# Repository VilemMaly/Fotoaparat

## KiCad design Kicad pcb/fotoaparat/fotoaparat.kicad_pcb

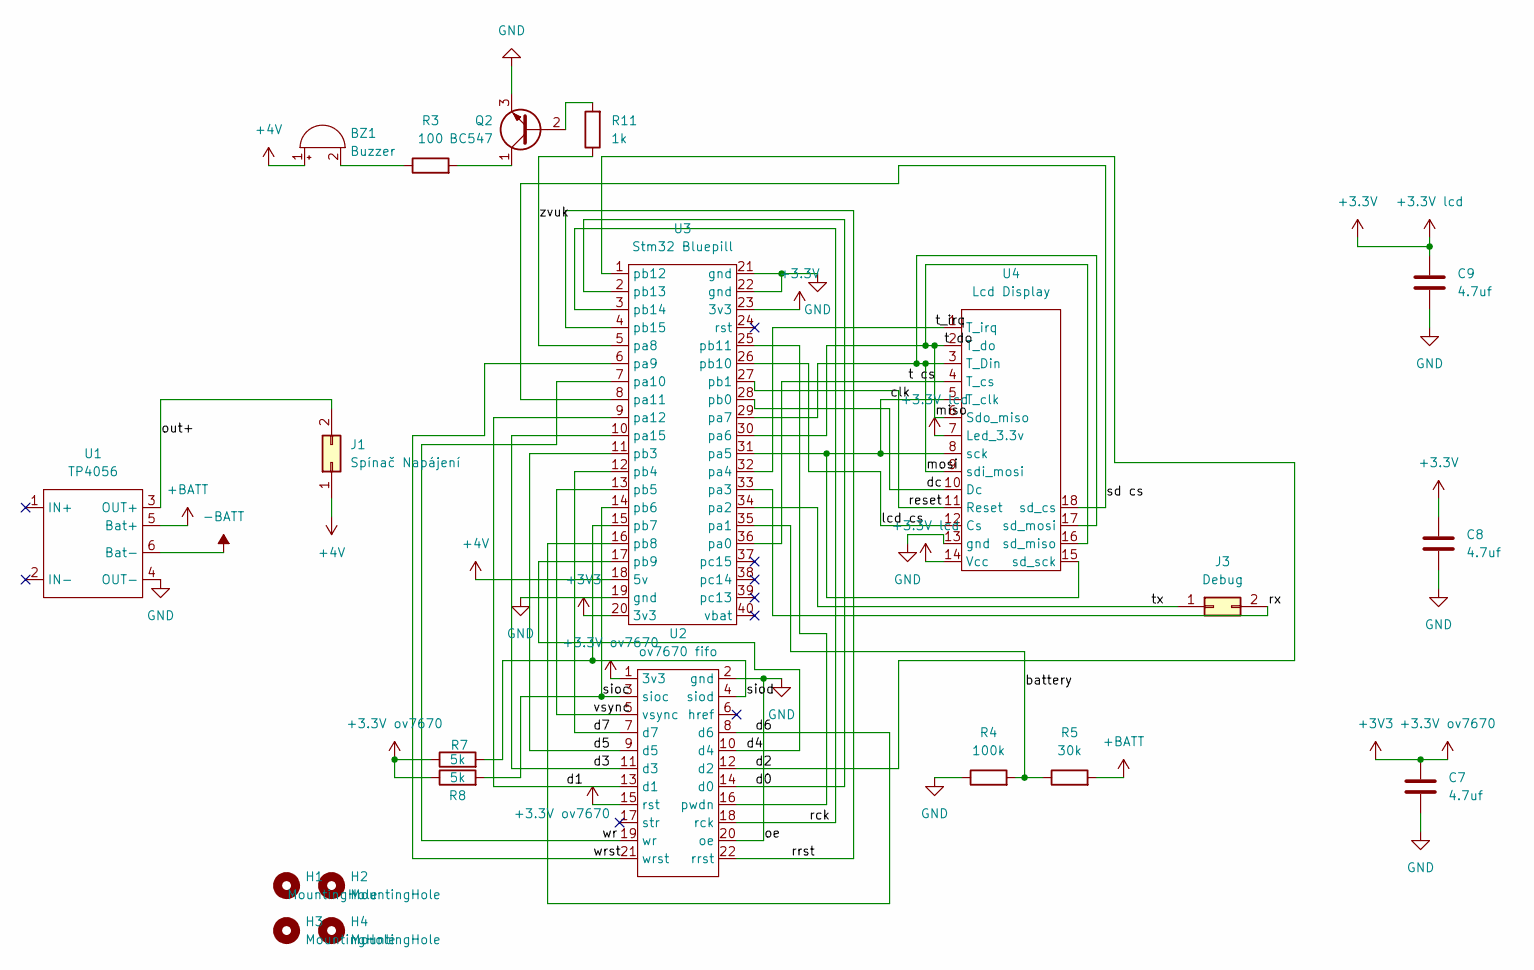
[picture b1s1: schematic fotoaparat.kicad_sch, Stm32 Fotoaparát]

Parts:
BZ1: Buzzer; Jiangsu
C7, C8, C9: 4.7uf; kondenzator
H1, H2, H3, H4: MountingHole; MountingHole_3.2mm_M3
J1: Spínač Napájení; txrx
J3: Debug; txrx
Q2: BC547; npnTHT
R3: 100; thtRESISTOR
R4: 100k; thtRESISTOR
R5: 30k; thtRESISTOR
R7, R8: 5k; thtRESISTOR
R11: 1k; thtRESISTOR
U1: TP4056
U2: ov7670 fifo; ov7670
U3: Stm32 Bluepill; Bluepill
U4: Lcd Display; ili9341

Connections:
+3.3V: C8.1, C9.1, U3.23 (3v3), U4.7 (Led_3.3v), U4.14 (Vcc)
+3.3V ov7670: C7.1, R7.1, R8.1, U2.1 (3v3), U2.15 (rst), U3.20 (3v3)
+4V: BZ1.1 (+), J1.1, U3.18 (5v)
+BATT: R5.2, U1.5 (Bat+)
-BATT: U1.6 (Bat-)
/battery: R4.2, R5.1, U3.35 (pa1)
/clk: U3.31 (pa5), U4.5 (T_clk), U4.8 (sck), U4.15 (sd_sck)
/d0: U2.14 (d0), U3.2 (pb13)
/d1: U2.13 (d1), U3.9 (pa12)
/d2: U2.12 (d2), U3.1 (pb12)
/d3: U2.11 (d3), U3.10 (pa15)
/d4: U2.10 (d4), U3.17 (pb9)
/d5: U2.9 (d5), U3.11 (pb3)
/d6: U2.8 (d6), U3.16 (pb8)
/d7: U2.7 (d7), U3.12 (pb4)
/dc: U3.28 (pb0), U4.10 (Dc)
/lcd cs: U3.26 (pb10), U4.12 (Cs)
/miso: U3.30 (pa6), U4.2 (T_do), U4.6 (Sdo_miso), U4.16 (sd_miso)
/mosi: U3.29 (pa7), U4.3 (T_Din), U4.9 (sdi_mosi), U4.17 (sd_mosi)
/out+: J1.2, U1.3 (OUT+)
/rck: U2.18 (rck), U3.3 (pb14)
/reset: U3.27 (pb1), U4.11 (Reset)
/rrst: U2.22 (rrst), U3.4 (pb15)
/rx: J3.2, U3.33 (pa3)
/sd cs: U3.8 (pa11), U4.18 (sd_cs)
/sioc: R8.2, U2.3 (sioc), U3.14 (pb6)
/siod: R7.2, U2.4 (siod), U3.15 (pb7)
/t cs: U3.36 (pa0), U4.4 (T_cs)
/t_irq: U3.32 (pa4), U4.1 (T_irq)
/tx: J3.1, U3.34 (pa2)
/vsync: U2.5 (vsync), U3.13 (pb5)
/wr: U2.19 (wr), U3.7 (pa10)
/wrst: U2.21 (wrst), U3.6 (pa9)
/zvuk: R11.1, U3.5 (pa8)
GND: C7.2, C8.2, C9.2, Q2.3 (E), R4.1, U1.4 (OUT-), U2.2 (gnd), U2.20 (oe), U3.19 (gnd), U3.21 (gnd), U3.22 (gnd), U4.13 (gnd)
unnamed: BZ1.2 (-), R3.1
unnamed: Q2.2 (B), R11.2
unnamed: Q2.1 (C), R3.2
unnamed: U2.16 (pwdn), U3.25 (pb11)

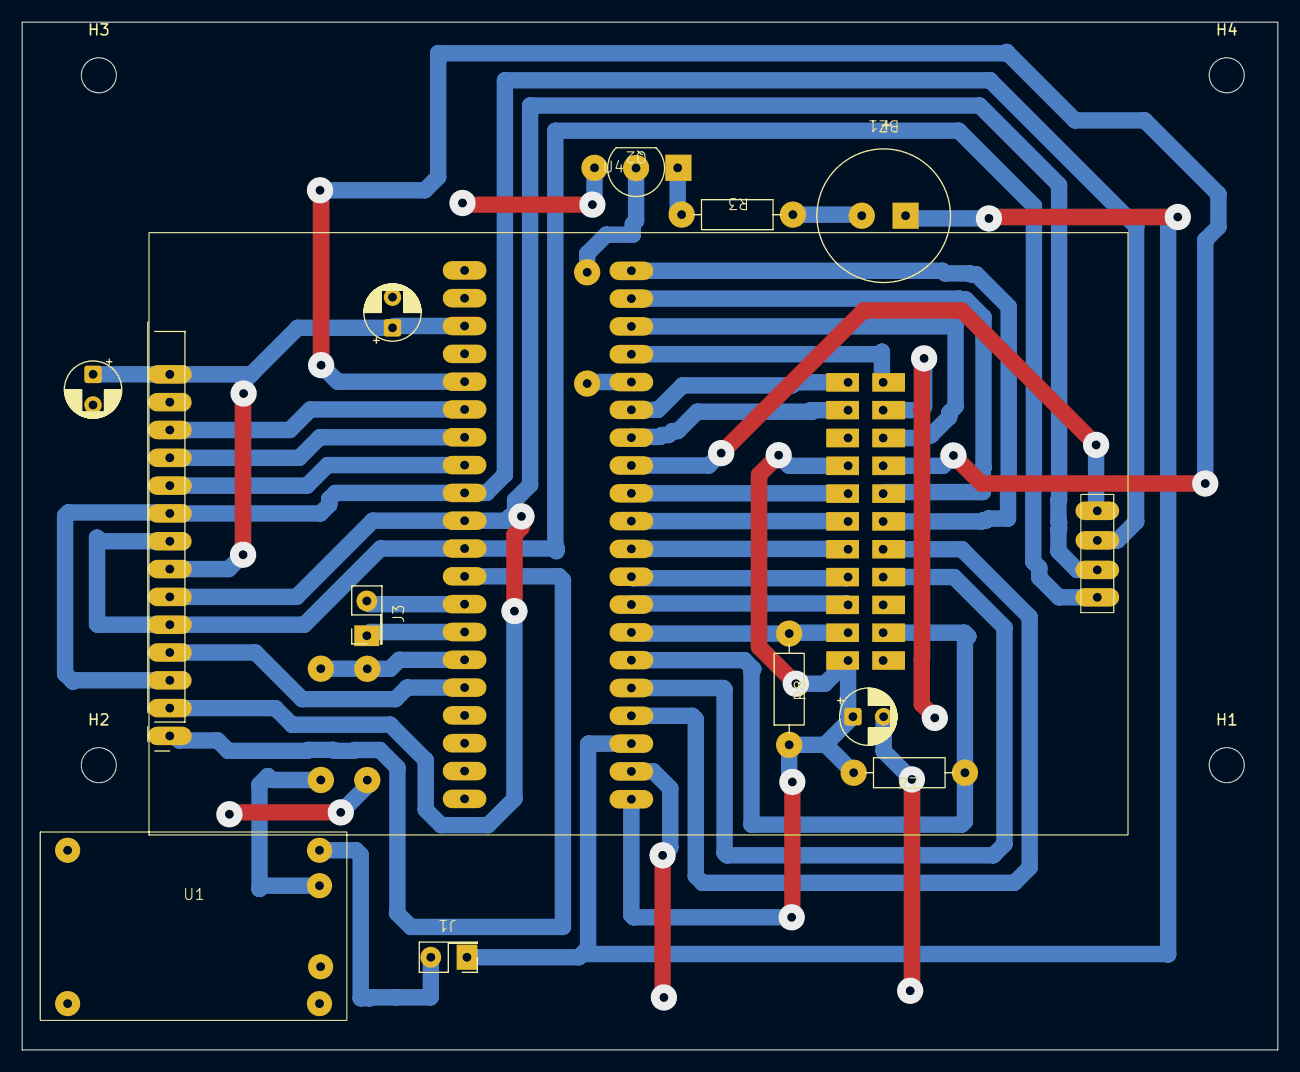
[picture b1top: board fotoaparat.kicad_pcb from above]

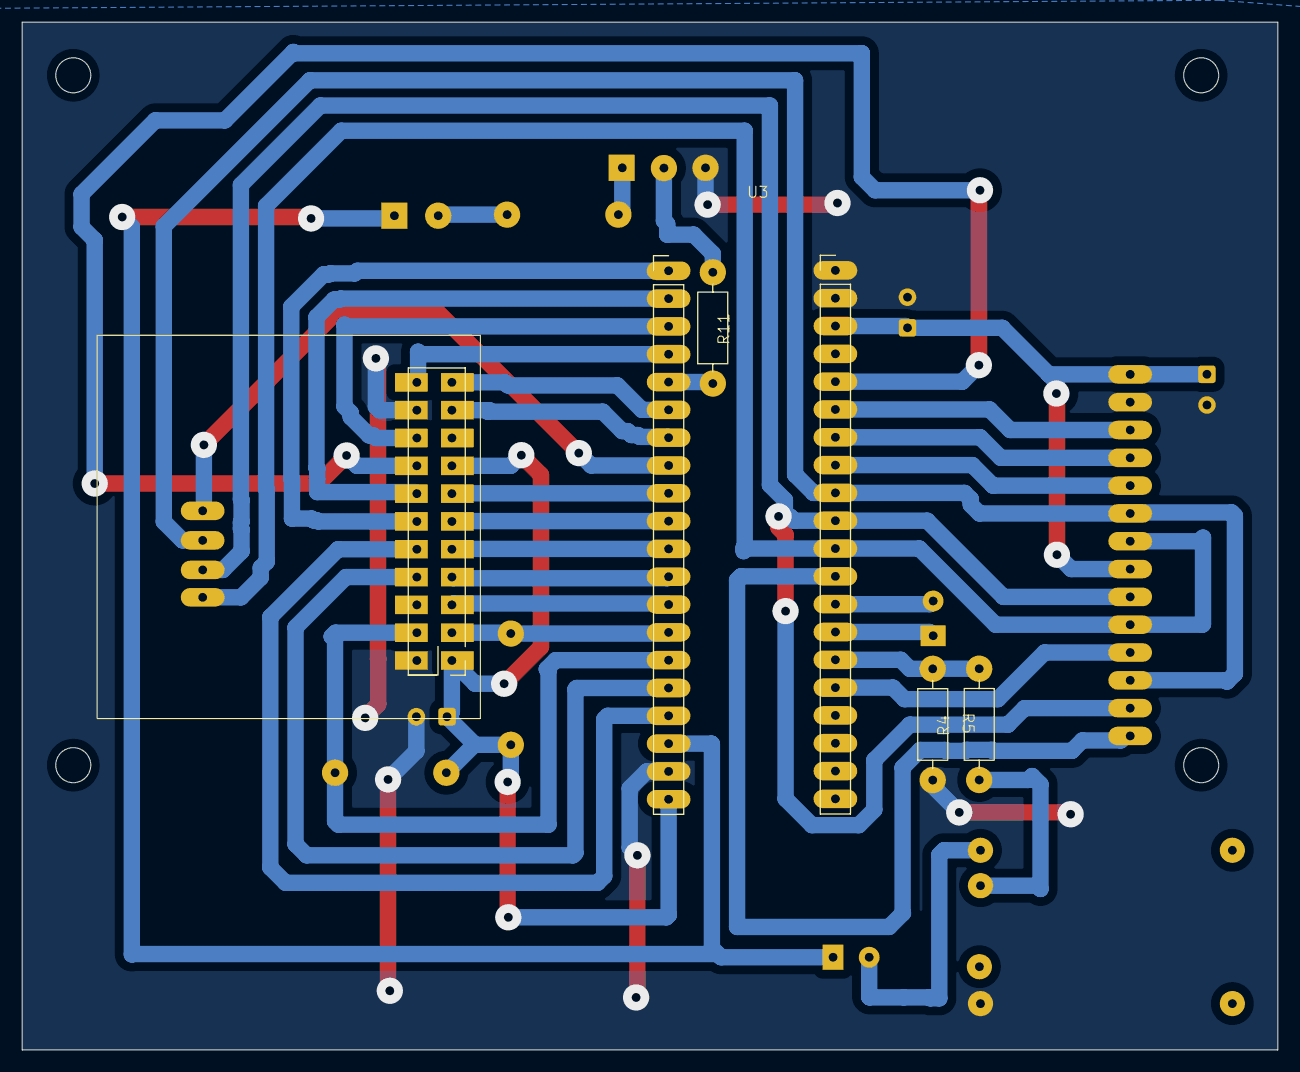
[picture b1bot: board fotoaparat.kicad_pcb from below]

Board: 2 copper layers, 114.7 x 93.8 mm, 21 parts (5 on the bottom side), 38 nets.

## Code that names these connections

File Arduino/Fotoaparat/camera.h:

#pragma once
#include "FifoCamera.h"

#define VSYNCSTATUS() (GPIOB->IDR >> 5) & 1

const int VSYNC = PB5;   // vsync
const int SIOD  = PB7;   // siod (SDA)
const int SIOC  = PB6;   // sioc (SCL)


const int RCK  = PB14;   // read clock
const int RRST = PB15;   // read reset
const int WR   = PA10;   // write enable
const int WRST = PA9;    // write reset

//OE -> GND     (output enable always on since we control the read clock)
//PWDN not nonnected  
//HREF not connected
//STR not connected
//RST -> 3.3V 

const int DAT0 = PB13;  // D0
const int DAT1 = PA12;  // D1
const int DAT2 = PB12;  // D2
const int DAT3 = PA15;  // D3
const int DAT4 = PB9;   // D4
const int DAT5 = PB3;   // D5
const int DAT6 = PB8;   // D6
const int DAT7 = PB4;   // D7

//#define QQVGA
//#define QQQVGA
#define QVGA
#ifdef QVGA
const int XRES = 320;
const int YRES = 240;
#endif

#ifdef QQVGA
const int XRES = 160;
const int YRES = 120;
#endif
#ifdef QQQVGA
const int XRES = 80;
const int YRES = 60;
#endif

const int BYTES_PER_PIXEL = 1;
const int frameSize = XRES * YRES * BYTES_PER_PIXEL;

using ov7670 = FifoCamera<RRST, WRST, RCK, WR, DAT0, DAT1, DAT2, DAT3, DAT4, DAT5, DAT6, DAT7>;

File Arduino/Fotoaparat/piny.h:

#pragma once
#include <Arduino.h>

// TFT
#define TFT_CS    PB10
#define TFT_DC    PB0
#define TFT_RST   PB1

// Touch
#define TOUCH_CS  PA0
#define TOUCH_IRQ PA4

// SD
#define SD_CS     PA11

// Battery + sound
#define BATTERY   PA1
#define ZVUK      PA8
#define VSYNCCAMERA PB5

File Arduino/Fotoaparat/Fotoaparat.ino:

#include <SPI.h>
#include <SdFat.h>
#include "SDkarta.h"
#include "Adafruit_GFX.h"         // Adafruit Graphics library
#include <TFT_eSPI.h>
#include <XPT2046_Touchscreen.h>
#include "piny.h"
#include "I2C.h"
#include "xpt.h"
#include "menu.h"
#include "I2C.h"
#include "camera.h"
#include "stm32f1xx_hal.h"

TFT_eSPI tft = TFT_eSPI(); // Vytvoření objektu

XPT2046_Touchscreen touch(TOUCH_CS, TOUCH_IRQ);

HardwareSerial Serial3(PA3, PA2); // RX, TX

OV7670_I2C i2c(PB7, PB6);

SDkarta sdkarta(tft);

ov7670 camera(i2c, sdkarta);

xpt dotek = xpt(touch, sdkarta);

void setup() 
{
  Serial3.begin(500000);
  Serial3.println("Initialization...");

  __HAL_RCC_AFIO_CLK_ENABLE();

  // vypne JTAG, nechá SWD
  MODIFY_REG(AFIO->MAPR, AFIO_MAPR_SWJ_CFG, AFIO_MAPR_SWJ_CFG_1);

  pinMode(PB11, OUTPUT);
  pinMode(VSYNC, INPUT);
  pinMode(TFT_CS, OUTPUT);
  pinMode(SD_CS, OUTPUT);
  pinMode(TOUCH_CS, OUTPUT);

  digitalWrite(PB11, LOW);   // PWDN = 0
  pinMode(TFT_RST, OUTPUT);
  digitalWrite(TFT_RST, LOW);
  digitalWrite(TFT_RST, HIGH);
  spiAllHigh();
  delay(10);

  // zbytek setupu
  i2c.init();
  //i2c.scan();
  

  camera.init();
  #ifdef QVGA
  camera.QVGARGB565();  
  #endif

  #ifdef QQVGA
  camera.QQVGARGB565();
  #endif

  //camera.RGBRaw();
  //camera.testImage();

  Serial3.println( i2c.readRegister(0x12), HEX);
  Serial3.println( i2c.readRegister(0x71), HEX);
  Serial3.println("start");

  spiTFT();
  delay(10);
  tft.init();
  tft.setSwapBytes(true);
  tft.setRotation(3);
  tft.fillScreen(0);

  delay(10);
  spiTouch();
  touch.begin(tft.getSPIinstance());
  delay(10);

  spiSD();
  sdkarta.begin();
  delay(10);
  if(sdkarta.readSetting("calibrate", 0) == 1)
    {
    dotek.autoCalibrate();
    }
  dotek.setCalibration();

  initBattery();

  camera.loadSettings();

}

void loop() 
{
  //frameToSerial3();
  spiTouch();
  delay(10);
  int timePress = dotek.touchedMs(500);
  if (timePress > 0 && timePress < 500) {
    camera.yuv();
    tone(ZVUK, 2000, 100);
    //sdkarta.prehrajZvuk("shutter.raw");

    // Časovač pro SD operaci
    unsigned long sdStart = millis();
    String name = String(millis()) + "yuv";

    if(sdkarta.readSetting("rgb565", 0) == 1)
    {
      camera.BinToSD(String(name + "rgb565.bmp").c_str(), XRES, YRES, 2, sdkarta);
    }
    
    camera.YUVtoSD(name.c_str(), XRES, YRES, 2, sdkarta);
    unsigned long sdDuration = millis() - sdStart;
    if(sdkarta.readSetting("postProcessYUV", 0) == 1)
    {
      sdkarta.yuvToRGB(name.c_str(), XRES, YRES);
      sdkarta.remove(name.c_str());
    }
    //sdkarta.convertRGB565Endian(name.c_str(), 40);
    //sdkarta.swapRGB565Bytes(name.c_str(), 40);
    Serial3.println("SD trvala ");
    Serial3.print(sdDuration);
    Serial3.println(" ms");
    camera.rgb();
    
    //camera.FrameToSerial(Serial3, XRES, YRES);

  }
  else if( timePress >= 500)
  {

    menu Menu = menu(tft, dotek, sdkarta, camera);
    Menu.enter();
    camera.loadSettings();

  }
    spiTFT();
    showBattery();
    unsigned long lcdStart = millis();
    // čekej na konec předchozího frame
    while(VSYNCSTATUS());

    // čekej na začátek frame
    while(!VSYNCSTATUS());

    // připrav FIFO (RST)
    camera.prepareCapture();

    // začni zapisovat
    camera.startCapture();

    // čekej na konec frame
    while(VSYNCSTATUS());

    // zastav zápis
    camera.stopCapture();

    // teď čti FIFO
    camera.FrameToDisplay(tft, XRES, YRES);

    //camera.testFifo(XRES, YRES);
    unsigned long lcdDuration = millis() - lcdStart;
    Serial3.print("LCD trvala ");
    Serial3.print(lcdDuration);
    Serial3.println(" ms");
  
}

// Rozměry a pozice baterie
#define BATTERY_X 250
#define BATTERY_Y 10
#define BATTERY_WIDTH 40
#define BATTERY_HEIGHT 20
#define BATTERY_PADDING 2

// Barvy
#define BATTERY_FRAME_COLOR TFT_WHITE
#define BATTERY_OK_COLOR    TFT_GREEN
#define BATTERY_BAD_COLOR   TFT_RED
#define BATTERY_BG_COLOR    TFT_BLACK

// ADC
#define ADC_MAX 4095
#define ADC_TOLERANCE 5

void showBattery()
{
    int adcValue = analogRead(BATTERY);

    // ±5 kroků kolem 3.3 V
    bool ok = (adcValue >= (ADC_MAX - ADC_TOLERANCE)) &&
              (adcValue <= ADC_MAX);

    uint16_t fillColor = ok ? BATTERY_OK_COLOR : BATTERY_BAD_COLOR;

    // vymazání oblasti
    tft.fillRect(BATTERY_X, BATTERY_Y,
                 BATTERY_WIDTH + 4, BATTERY_HEIGHT,
                 BATTERY_BG_COLOR);

    // rámeček
    tft.drawRect(BATTERY_X, BATTERY_Y,
                 BATTERY_WIDTH, BATTERY_HEIGHT,
                 BATTERY_FRAME_COLOR);

    // pól baterie
    tft.fillRect(BATTERY_X + BATTERY_WIDTH,
                 BATTERY_Y + BATTERY_HEIGHT / 4,
                 3, BATTERY_HEIGHT / 2,
                 BATTERY_FRAME_COLOR);

    // plná výplň – jen barva
    tft.fillRect(BATTERY_X + BATTERY_PADDING + 1,
                 BATTERY_Y + BATTERY_PADDING + 1,
                 BATTERY_WIDTH - 2 * BATTERY_PADDING - 2,
                 BATTERY_HEIGHT - 2 * BATTERY_PADDING - 2,
                 fillColor);

    tft.setTextColor(TFT_WHITE, fillColor);
    tft.setTextDatum(MC_DATUM);
    tft.setTextSize(2);     // ← použití velikosti textu

    tft.drawString(
        String(adcValue),
        BATTERY_WIDTH - 2 * BATTERY_PADDING - 2,
        BATTERY_HEIGHT - 2 * BATTERY_PADDING - 2
    );
}

void initBattery()
{
    pinMode(BATTERY, INPUT_ANALOG);
    analogReadResolution(12);
    showBattery();
}

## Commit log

2025-09-30 Import komponent do schémata pcb
2025-10-01 První zapojení
2025-10-01 Zapojení kamery tlačítek debug pinů atd
2025-10-02 Lcd Konektor
2025-10-02 Baterie
2025-10-05 Přepojení součástek
    vypadá to trochu lépe
2025-10-06 Baterie nabíječka
2025-10-06 Regulátory
2025-10-07 Oprava chyb a volné konektory
2025-10-08 Buzzer
2025-10-08 Úprava knihoven
2025-10-09 Začátek návrhu pcb desky
2025-10-10 Outline desky
2025-10-10 První pcb spoje
2025-10-10 První prototyp pcb
2025-10-11 Drobné změny
2025-10-13 Pokus o druhý prototyp
2025-10-14 Téměř dokončený 2 prototyp
2025-10-14 Druhá deska pcb
    Signálové trasy jsou víc daleko od sebe a napájecí trasy jsou více široké než v minulém designu, to by mělo zmírnit elektromagnetickou interferenci.
2025-10-16 Příprava na výrobu pcb
    Gerber soubory se pravděpodobně ještě změní
2025-10-18 Oprava chyb
2025-10-19 Připraveno na výrobu
2025-11-17 Úprava designu
2025-11-18 Úprava schémata
2025-11-19 Gnd plane
2025-11-20 Resistory
2025-11-21 Úprava schéma
2025-11-24 Menší deska a větší plošky pro pájení
2025-11-28 Úprava chyb v schématu
2025-11-30 Úprava dps
2025-12-01 Zarovnání
2025-12-11 Opačný směr konektoru
2025-12-17 Zjednodušení schéma a oprava chyb
2025-12-27 Změna pinů a dps
2026-01-12 Dokončující úpravy
2026-02-08 Menu nastavení atd
    Docela dost nových funkcí v kódu
2026-03-16 obal ve freecad
2026-06-04 Nový model obalu, upravená dps, a "glitch" režim
2026-06-09 Bugfix
